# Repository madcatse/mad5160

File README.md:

Добро пожаловать в моqй проект по созданию реплики материнской платы IBM 5160, или как её называют - PC XT. 

**Предыстория**

Как-то вечером, глядя видеоролик Adrain Digital Basement о ремонте оригинальной IBM CGA видеокарты, обратил внимание что в ролике он демонстрировал схему всей видеокарты, которую кто-то выполнил в KiCAD. И упомянул, что схема иначально взята из оригинальной документации самой IBM. У меня сразу возникла мысль - а могу ли я сделать реплику такой видеокарты, раз уже проверенная схема есть в наличии?
Быстрый поиск показал что да, такая схема доступна, а также что кто-то уже сделал реплику CGA видеокарты (проект CGA Redux). Глядя на разведенную карточку, в голову проникла мысль: если есть схема видеокарты от IBM, то наверное есть схема и от материнской платы? И да - IBM 5160 Technical Reference от Апреля 1983 года действительно содержит схему на 11 листах всей материнской платы. Ну а если есть схема - то насколько сложным будет взять её и развести? Сделать реплику. Так появился данный проект.

**Начало работ и поиск подводных камней**

Вооружившись документацией из Technical Reference я принялся за работу. Нашел и скачал всю доступную документацию на 5160, разобрал, и проанализировал. Нашел фотографии материнской платы (спасибо retroweb), с которых бралась визуальная информация по компонентам. 

Потом выписал список всех компонентов на плате, с которыми предстояло работать. В этот список попали:

*центральный процессор и микросхемы, которые составляли его обвязку (чип сет, понимаете?)

*микросхемы памяти, которыми набиралась оперативная память (от 16 килобайт до 256 килобайт)

*микросхемы логики, по большей части представленные 74LS и 74S сериями

*микросхемы ПЗУ, по счастью две обычные 27С256 EPROM

*двойной периферийный драйвер SN75477P

*PAL-чип U44

*мимикрирующие под микросхемы резисторные сборки в DIP-корпусах (RN1-RN5)

*две временные задержки TD1 и TD2

*сравнительно небольшое разнообразие резисторов и конденсаторов, а также кварцевый резонатор

*стандартные 62-пиновые слоты, DIN5-коннектор под клавиатуру и Molex коннектор питания.

**С чем не было проблем**

Меньше всего проблем принес центральный процессор и его обвязка: 
Центральный процессор 8088 (совесткий аналог КР1810ВМ88)
Математический сопроцессор 8087 (чудовищно редкий совесткий аналог КР1810ВМ88)
Программируемый DMA контроллер 8237A (совесткий аналог КР1810ВТ37А)
Программируемый таймер 8253 (совесткий аналог КР580ВИ53Д)
Программируемый интерфейс периферийных устройств 8255A (совесткий аналог КР580ВВ55А)
Программируемый контроллер прерываний 8259A (совесткий аналог КР1810ВН59А)
Генератор частоты 8284A (совесткий аналог КР1810ГФ84А)
Контроллер шины M8288 (совесткий аналог КР1810ВГ88)
Все эти микросхемы сравнительно легкодоступны и их приобретение и проверка не составила никакого труда.

Микросхемы памяти также представляют собой совершенно стандартные 4164/41256 и также не вызывают проблем с их приобретением и проверкой.

То же самое касается и микросхем логики - 74 серия и её советские клоны достаточно распространены, легко приобретаются и проверяются. Неприятность в общем разнообразии микросхем. Для сборки Вам потребуются: 
7407.

74LS00,
74LS04,
74LS04,
74LS10,
74LS20,
74LS27,
74LS32,
74LS138,
74LS158,
74LS175,
74LS243,
74LS244,
74LS245,
74LS322,
74LS373,
74LS670.

74S00,
74S08,
74S74,
74S280.

Часть совершенно свободно находится на aliexpress, часть есть там же, но поддельная, часть найти будет сложно, особенно S-чипы. Но это реализуемо.

Двойной периферийный драйвер _SN75477P_ не относится к 74ой серии, но также легко доступен.

Пассивные компоненты, кварцевый резонатор, подстроеный конденсатор, слоты ISA и коннектор DIN5 для подключения клавиатуры также совершенно стандартные. 

**Проблемы**

Все это касалось комплектующих, с которыми никаких принципиальных проблем не было. К сожалению, это не все компоненты на плате. Есть часть, с которыми проблемы были, и которые пришлось решать.

**PAL 82S129N (U44)**

Злосчастная U44, на месте которой располагается PAL-чип 82S129N, программируемая логическая микросхема декодера памяти. 

Обширный поиск показал отсутствие легкодоступного дампа содержимого данной микросхемы. Однако с давных времен (декабрь 1989 года!) существует мод, 1megXT, который позволяет поставить на старые 5160-материснкие платы до 1 мегабайта памяти, и заключается в замене вышеуказанной 82S129N на GAL16V8 с хорошо задокументированной зашивкой, плюс установке одной дополнительной микросхемы. Установка такого мода мало того что решает проблему с отсутствием зашивки, так ещё и позволяет учетвертить доступный объем оперативной памяти! Хоть я и хотел поиграться с PC с 16кб памяти (минимально возмомжный объем), но как вышло так вышло. 
Для реализации этого мода Вам потребуется одна микросхема GAL16V8 и зашивка для неё. Зашивка с уравнениями присутствует в каталоге firmware\GAL16V8 Там же есть ссылка на оригинальный тред на vcfed. Микросхема GAL16V8 длиннее, чем оригинальная 82S129N, поэтому установить её напрямую не получится. Установите панель на место U44, после чего посадите GAL16V8 так чтобы в панель вошли первый и последний вины, а "хвост" остался висеть в воздухе. Поднимите пины, которые не попали в сокет, и поставьте перемычку между 8 и 10 пинами (это соединит пин земли на GAL16 и пин земли сокета). 

Обратите внимание, что в моем случае я использовал **не свою замену резистороной сборки**, а **оригинальную резисторную сборку**. Так как плата была тестовая, то резисторая сборка ставилась в панель, и она будет мешать моду, не позволяя поставить его по высоте. Надо либо паять плату сборки под основание платы, без панели, либо поднимать микросхему мода несколькими панельками. Если делать без панельки под резисторную сборку, места должно хватить.
После этого мод готов к работе, останется установить джампер на E2 и на блоке SW2 третьим и четвертым переключателем задать необходимый объем оперативной памяти (подробнее см. документацию на мод в файле \firmware\1megXT.txt)

**Резисторные сборки**

IBM установил на плате пять резисторных сборок в DIP-16 корпусах. Это:

RN1, RN5 - 15 резисторов по 4.7 кОм

RN3, RN4 - 8 резисторов по 30 Ом

RN2 - 15 резисторов по 8.2 кОм

Частично такие сборки можно купить, но цены на них очень и очень негуманные. Некоторые (8 по 30) имеют неходовой номинал и представляют собой проблему. Чтобы не заморачиваться с поиском такой экзотики я создал проект "RNDip16", располагающийся в папке \supporting_prj\RNDip16
Проект представляет собой две небольшие платы, по габаритам схожими с футпринтом микросхемы в корпусе DIP-16, на которые можно установить 8 либо 15 SMD-резисторов любого номинала, в корпусе 0805. 

После пайки резисторов следует запаять пины ножек и замена резисторной сборки готова. 

Установка такой замены допускается в сокет, либо напрямую запайкой в плату. Gerber-файлы лежат в папке \supporting_prj\RNDip16\gerbers

**Линии временной задержки TD1 и TD2**

Довольно экзотические компоненты установлены под обозначениями TD1 и TD2. Данные компоненты обеспечивают контролируемую задержку сигнала и являются критичными для корректной работы компьютера. По счастью само IBM в документации от 1986ого года выбросил из схемы TD2, заменив её обычным резистором, убрав резисторы R4 и R5. Но вот TD1 осталась, как и проблемы с ней. Часто на её месте стоят компоненты от BELFUSE 0447-0100-98, либо SPRAGUE 61Z14A100. Это линия задержки на 5 выходов, каждый из которых добавляет 20нс к времени выхода сигнала. На ebay такие компоненты можно купить, однако у нас в настоящий момент это исключено. 

Поиск показал что существуют современные вариации таких задержек - DS1100Z-100 в корпусе NSOIC-8. Я создал проект time_delay, расположенный по пути \supporting_prj\time_delay ,который представляет собой крошечную плату с габаритами исходной временной задержки, на которую необходимо напаять DS1100Z-100 и пины, после чего данный компонент на 100% заменяет исходную временную задержку. 

Gerber-файлы лежат в папке \supporting_prj\time_delay\Gerbers

**Коннектор питания P8/P9**

Старый-добрый AT-коннектор питания (что, получается, неверно, так как у нас XT и этот тип коннектора должен тогда называться XT-коннектор). 

Его можно взять с донорской материнской платы, но я решил поставить современный вариант. Molex 26604060, имеет такие же габариты, но пины квадратной, а не плоской формы. 

Однако типовой AT-блок питания подключается без проблем, и нет нужды искать донора.

**BIOS**

Микросхемы биоса используются совершенно стандартные, 27C256. В одной находится сам биос, в другой - ром с IBM BASIC. Все оригинальные BIOS есть здесь: https://www.minuszerodegrees.net/bios/bios.htm
Также можно использовать различные сторонние BIOS, в частности биос от TurboXT, доступный по пути firmware\turboxt\turboxt.bin

**Ошибки в схеме**

Первая ревизия платы (версия 0.1) содержала в себе ошибку, связанную с опечаткой в оригинальной IBM документации. Для сравнения, фрагмент схемы 1983 года:

Тот же участок в схеме от 1986 года:

Из-за этого линия проверки четности на ISA-слоте была подтянута на +5 постоянно через резистор, и система ВСЕГДА при старте определяла ошибку четности. Это единственный фикс, который потребовалось сделать в схеме после того как был изготовлен, собран и испытан первый образец.

**Печатная плата**

Печатную плату я разводил используя в качестве ориентира скан платы, любезно предоставленный пользователем jafir с форума vcfed, а также остальные референсные фото. Так как оригинальная плата четырехслойная, я не имел на руках оригинальной платы, и тем более не мог сделать послойную декомпозицию платы с целью анализа проводников на внутренних слоях платы, трассировка всех проводников выполнена с нуля. Сигнальные слои - F.Cu и B.Cu. Слой In1.Cu - +5В, слой In2.Cu - земля. Линии +12В, -12В и -5В проведены по сигнальным слоям. Контур платы, координаты посадочных отверстий, некоторые посадочные места компонентов (трехвыводные конденсаторы, пленочный конденсатор, подстроечный конденсатор) взяты из открытого проекта-реплики IBM PC 5150 (PC-Retro, MTM Scientific)

**Изготовление и сборка**

Четырехслойная печатная плата без каких либо особенностей. Изготовление возможно силами китайских производителей. Gerbar-файлы для изготовления находятся по пути \gerbers

**Благодарности**

Выражаю огромное спасибо за идею, помощь в проектировании и отладке:
Adrinan Black с канала Adrian Drigital Basement за идею, а также диагностический ром для памяти, который помог локализовать проблему с Parity

jafir с форума vcfed за качественный скан материнской платы

modem7 с форума vcfed за помощь в локализации проблемы и идеи по исправлению.

**Контакты**

Связаться со мной можно в телеграме, на моем небольшом канале:
https://t.me/madcatse

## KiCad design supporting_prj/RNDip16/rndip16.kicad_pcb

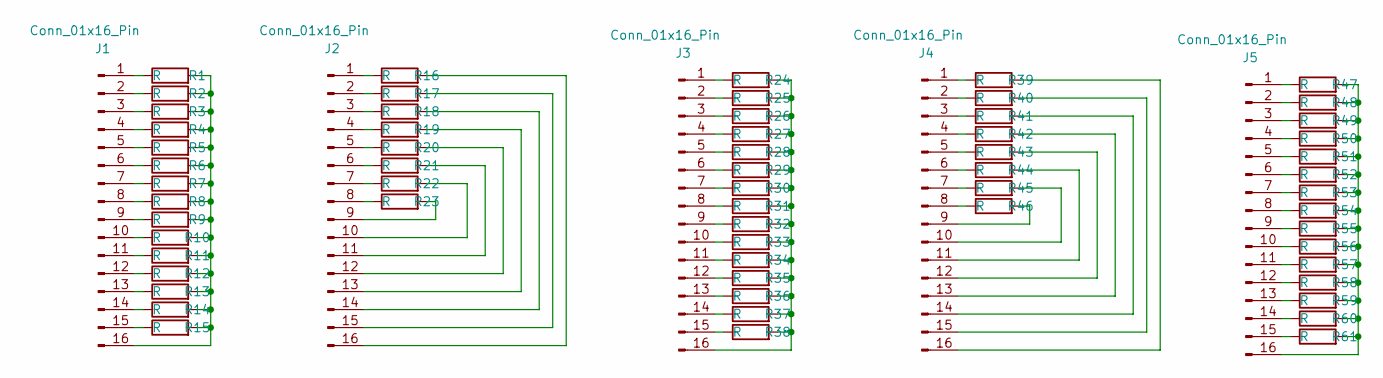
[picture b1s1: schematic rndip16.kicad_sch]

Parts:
J1, J2, J3, J4, J5: Conn_01x16_Pin; Dip16_package
R1, R2, R3, R4, R5, R6, R7, R8, R9, R10, R11, R12, R13, R14, R15, R16, R17, R18, R19, R20, R21, R22, R23, R24, R25, R26, R27, R28, R29, R30, R31, R32, R33, R34, R35, R36, R37, R38, R39, R40, R41, R42, R43, R44, R45, R46, R47, R48, R49, R50, R51, R52, R53, R54, R55, R56, R57, R58, R59, R60, R61: R; R_0805

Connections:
unnamed: J1.1, R1.1
unnamed: J1.2, R2.1
unnamed: J1.3, R3.1
unnamed: J1.4, R4.1
unnamed: J1.5, R5.1
unnamed: J1.6, R6.1
unnamed: J1.7, R7.1
unnamed: J1.8, R8.1
unnamed: J1.9, R9.1
unnamed: J1.10, R10.1
unnamed: J1.11, R11.1
unnamed: J1.12, R12.1
unnamed: J1.13, R13.1
unnamed: J1.14, R14.1
unnamed: J1.15, R15.1
unnamed: J1.16, R1.2, R2.2, R3.2, R4.2, R5.2, R6.2, R7.2, R8.2, R9.2, R10.2, R11.2, R12.2, R13.2, R14.2, R15.2
unnamed: J2.1, R16.1
unnamed: J2.2, R17.1
unnamed: J2.3, R18.1
unnamed: J2.4, R19.1
unnamed: J2.5, R20.1
unnamed: J2.6, R21.1
unnamed: J2.7, R22.1
unnamed: J2.8, R23.1
unnamed: J2.9, R23.2
unnamed: J2.10, R22.2
unnamed: J2.11, R21.2
unnamed: J2.12, R20.2
unnamed: J2.13, R19.2
unnamed: J2.14, R18.2
unnamed: J2.15, R17.2
unnamed: J2.16, R16.2
unnamed: J3.1, R24.1
unnamed: J3.2, R25.1
unnamed: J3.3, R26.1
unnamed: J3.4, R27.1
unnamed: J3.5, R28.1
unnamed: J3.6, R29.1
unnamed: J3.7, R30.1
unnamed: J3.8, R31.1
unnamed: J3.9, R32.1
unnamed: J3.10, R33.1
unnamed: J3.11, R34.1
unnamed: J3.12, R35.1
unnamed: J3.13, R36.1
unnamed: J3.14, R37.1
unnamed: J3.15, R38.1
unnamed: J3.16, R24.2, R25.2, R26.2, R27.2, R28.2, R29.2, R30.2, R31.2, R32.2, R33.2, R34.2, R35.2, R36.2, R37.2, R38.2
unnamed: J4.1, R39.1
unnamed: J4.2, R40.1
unnamed: J4.3, R41.1
unnamed: J4.4, R42.1
unnamed: J4.5, R43.1
unnamed: J4.6, R44.1
unnamed: J4.7, R45.1
unnamed: J4.8, R46.1
unnamed: J4.9, R46.2
unnamed: J4.10, R45.2
unnamed: J4.11, R44.2
unnamed: J4.12, R43.2
unnamed: J4.13, R42.2
unnamed: J4.14, R41.2
unnamed: J4.15, R40.2
unnamed: J4.16, R39.2
unnamed: J5.1, R47.1
unnamed: J5.2, R48.1
unnamed: J5.3, R49.1
unnamed: J5.4, R50.1
unnamed: J5.5, R51.1
unnamed: J5.6, R52.1
unnamed: J5.7, R53.1
unnamed: J5.8, R54.1
unnamed: J5.9, R55.1
unnamed: J5.10, R56.1
unnamed: J5.11, R57.1
unnamed: J5.12, R58.1
unnamed: J5.13, R59.1
unnamed: J5.14, R60.1
unnamed: J5.15, R61.1
unnamed: J5.16, R47.2, R48.2, R49.2, R50.2, R51.2, R52.2, R53.2, R54.2, R55.2, R56.2, R57.2, R58.2, R59.2, R60.2, R61.2

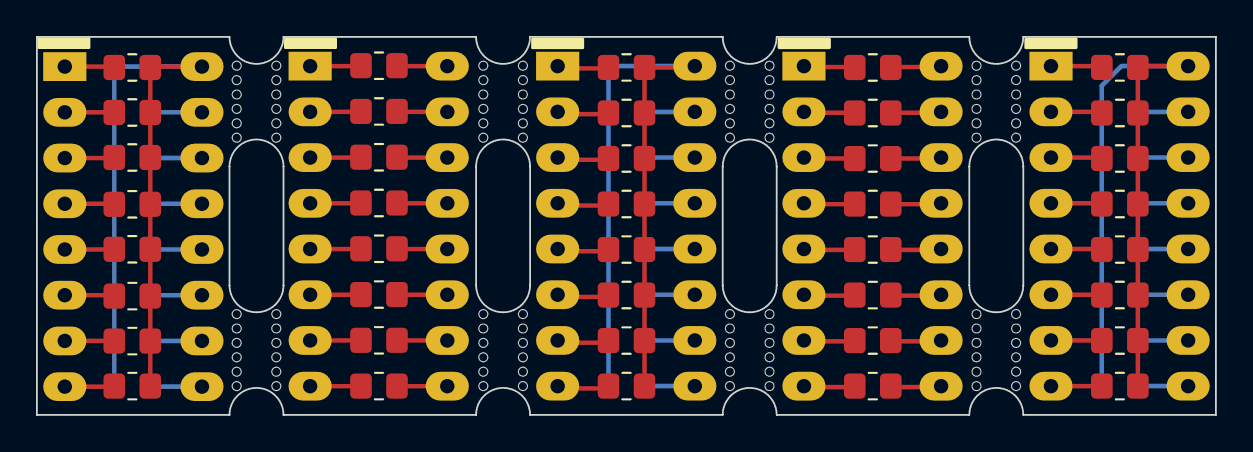
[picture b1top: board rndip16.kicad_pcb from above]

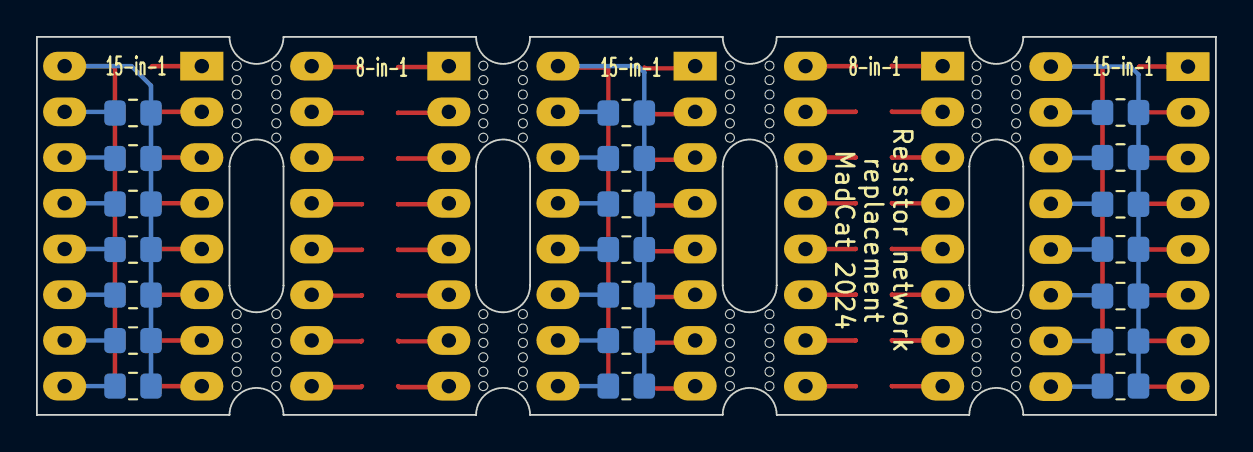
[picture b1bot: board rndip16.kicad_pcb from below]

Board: 2 copper layers, 65.5 x 21.0 mm, 74 parts (21 on the bottom side), 80 nets.

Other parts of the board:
mouse-bite-2.54mm-slot_13, mouse-bite-2.54mm-slot_13#2, mouse-bite-2.54mm-slot_13#3, mouse-bite-2.54mm-slot_13#4, mouse-bite-2.54mm-slot_13#5, mouse-bite-2.54mm-slot_13#6, mouse-bite-2.54mm-slot_13#7, mouse-bite-2.54mm-slot_13#8: VAL**; mouse_bite

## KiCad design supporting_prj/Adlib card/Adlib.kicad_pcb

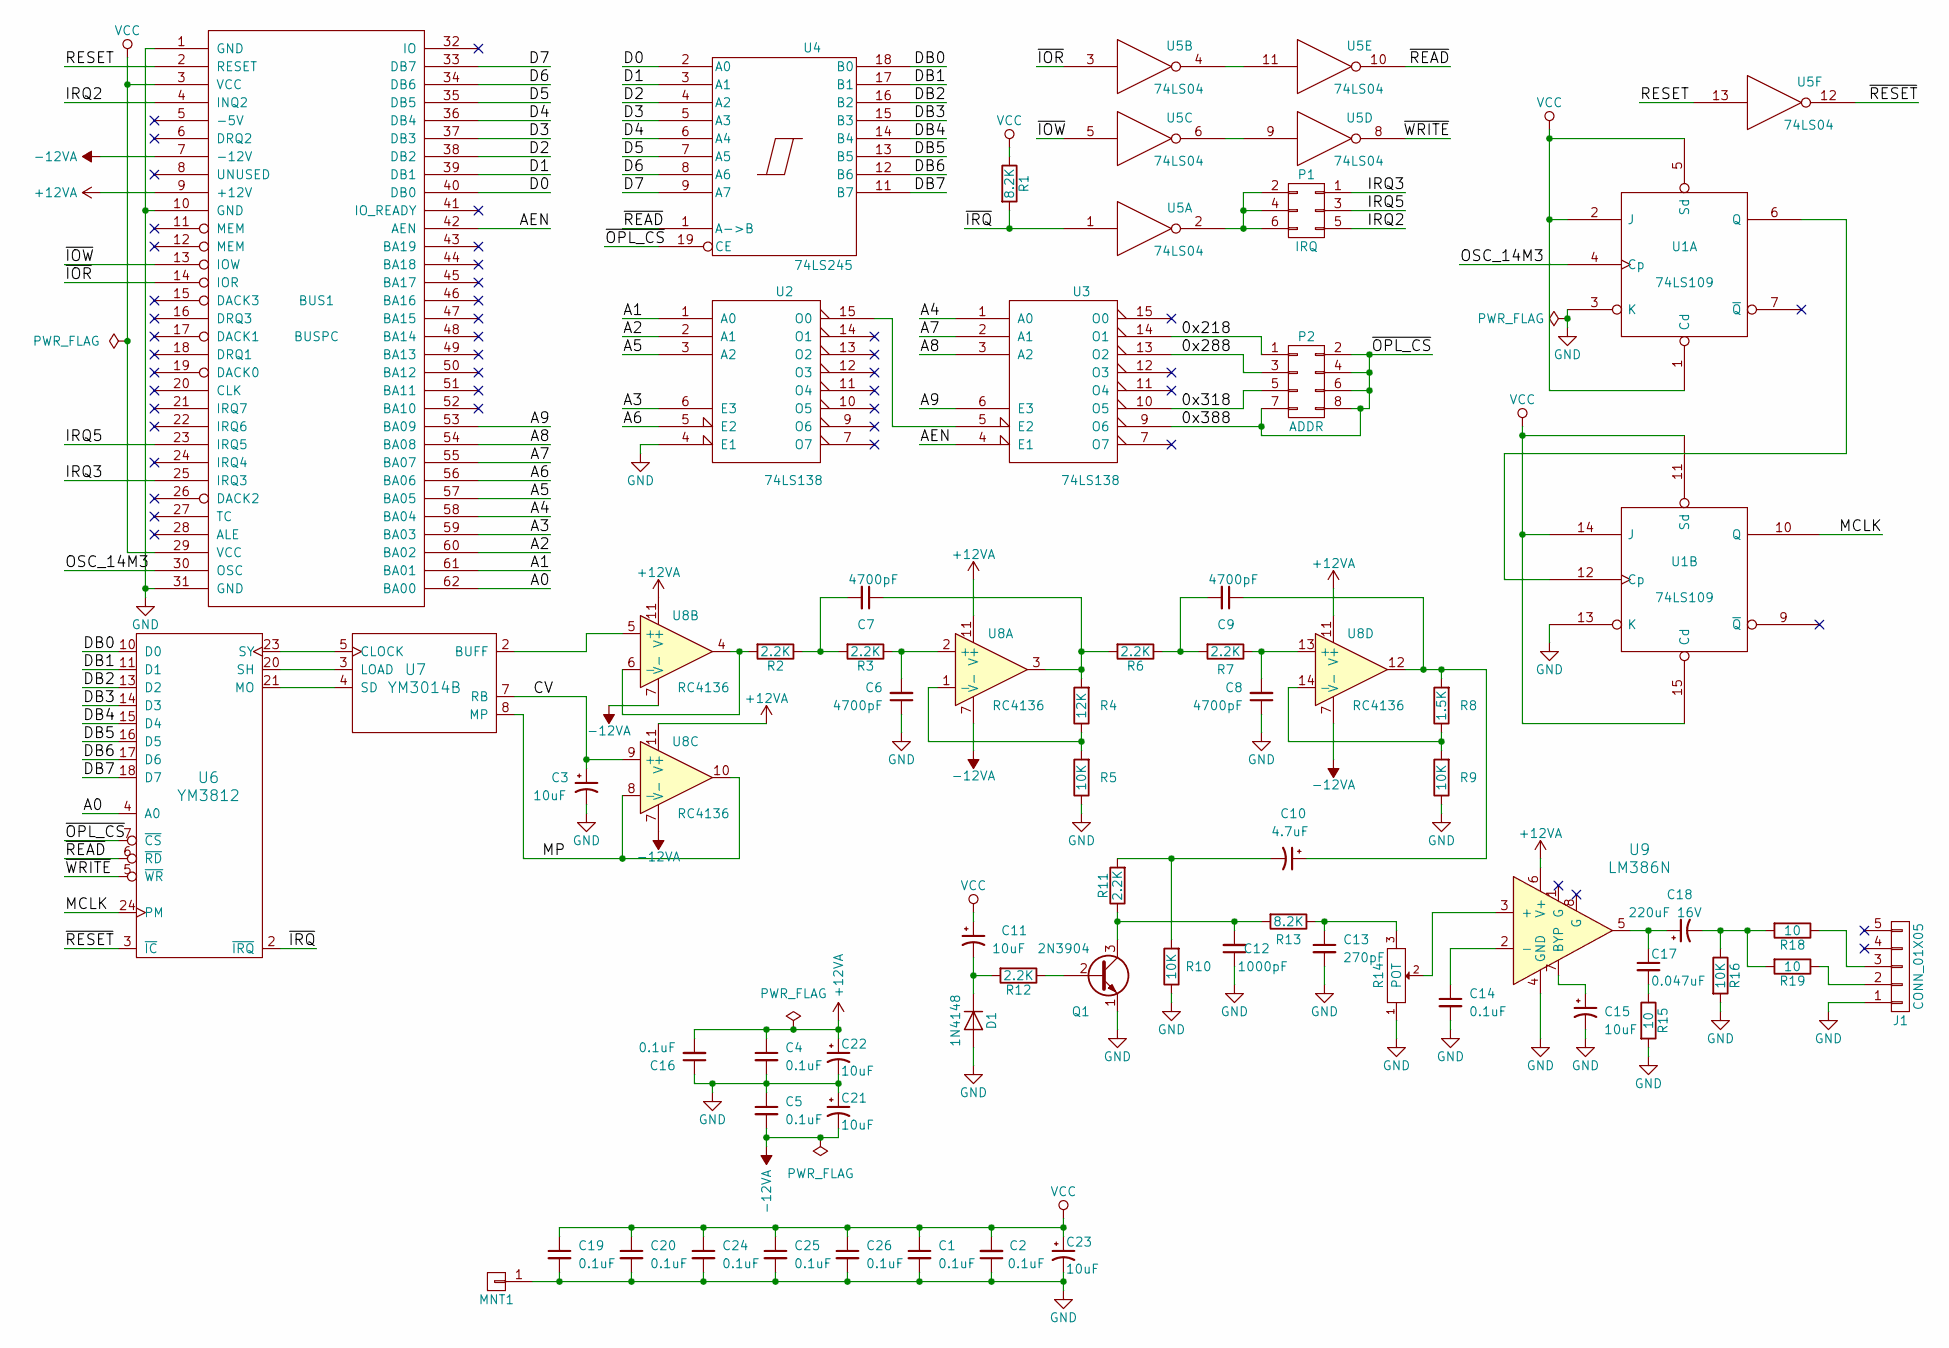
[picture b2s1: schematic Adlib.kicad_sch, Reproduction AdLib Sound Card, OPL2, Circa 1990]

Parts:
BUS1: BUSPC; BUS_PC_ADLIB
C1, C2, C4, C5, C14, C16, C19, C20, C24, C25, C26: 0.1uF; CAP23; Mouser 581-AR215C104K4R
C3, C11, C15, C21, C22, C23: 10uF; CAPAP200; Mouser 581-TAP106M025CRW
C6, C7, C8, C9: 4700pF; CAP23; Mouser 581-AR211C472K4R
C10: 4.7uF; CAPAP200; Mouser 581-TAP475K016SCS
C12: 1000pF; CAP23; Mouser 581-AR211C102K4R
C13: 270pF; CAP23; Mouser 594-S271K43SL0N6TK5R
C17: 0.047uF; CAP23; Mouser 581-AR215C473K4R
C18: 220uF 16V; CAPA1000; Mouser 647-TVX1C221MAD
D1: 1N4148; DIOA500; Mouser 512-1N4148
J1: CONN_01X05; JACK_CUI_SJ1-3553NG; Mouser 490-SJ1-3553NG
MNT1: CONN_01X01; MNT_KEYSTONE_9202; Mouser 534-9202
P1: IRQ; JMP3
P2: ADDR; JMP4
Q1: 2N3904; TO92-IL; Mouser 512-2N3904BU
R1, R13: 8.2K; RESA500; Mouser 291-8.2K-RC
R2, R3, R6, R7, R11, R12: 2.2K; RESA500; Mouser 291-2.2K-RC
R4: 12K; RESA500; Mouser 291-12K-RC
R5, R9, R10, R16: 10K; RESA500; Mouser 291-10K-RC
R8: 1.5K; RESA500; Mouser 291-1.5K-RC
R14: POT; RESV_BOURNS_91A1A; Mouser 652-91A1A-B24-D15L
R15, R18, R19: 10; RESA500; Mouser 291-10-RC
U1: 74LS109; DIP300_16N; Mouser 595-SN74LS109AN
U2, U3: 74LS138; DIP300_16N; Mouser 595-SN74LS138N
U4: 74LS245; DIP300_20N; Mouser 595-SN74LS245N
U5: 74LS04; DIP300_14N; Mouser 595-SN74LS04N
U6: YM3812; DIP600_24N
U7: YM3014B; DIP300_8N
U8: RC4136; DIP300_14N; Mouser 595-RC4136N
U9: LM386N; DIP300_8N; Mouser 926-LM386N-4/NOPB

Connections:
+12VA: BUS1.9 (+12V), C4.1, C16.2, C22.1, U8.11 (V+), U9.6 (V+)
-12VA: BUS1.7 (-12V), C5.2, C21.2, U8.7 (V-)
/0x218: P2.1, U3.14 (O1)
/0x288: P2.3, U3.13 (O2)
/0x318: P2.5, U3.10 (O5)
/0x388: P2.2, P2.4, P2.6, P2.7, P2.8, U3.9 (O6), U4.19 (CE), U6.7 (~CS)
/A0: BUS1.62 (BA00), U6.4 (A0)
/A1: BUS1.61 (BA01), U2.1 (A0)
/A2: BUS1.60 (BA02), U2.2 (A1)
/A3: BUS1.59 (BA03), U2.6 (E3)
/A4: BUS1.58 (BA04), U3.1 (A0)
/A5: BUS1.57 (BA05), U2.3 (A2)
/A6: BUS1.56 (BA06), U2.5 (E2)
/A7: BUS1.55 (BA07), U3.2 (A1)
/A8: BUS1.54 (BA08), U3.3 (A2)
/A9: BUS1.53 (BA09), U3.6 (E3)
/AEN: BUS1.42 (AEN), U3.4 (E1)
/CV: C3.1, U7.7 (RB), U8.9 (+)
/D0: BUS1.40 (DB0), U4.2 (A0)
/D1: BUS1.39 (DB1), U4.3 (A1)
/D2: BUS1.38 (DB2), U4.4 (A2)
/D3: BUS1.37 (DB3), U4.5 (A3)
/D4: BUS1.36 (DB4), U4.6 (A4)
/D5: BUS1.35 (DB5), U4.7 (A5)
/D6: BUS1.34 (DB6), U4.8 (A6)
/D7: BUS1.33 (DB7), U4.9 (A7)
/DB0: U4.18 (B0), U6.10 (D0)
/DB1: U4.17 (B1), U6.11 (D1)
/DB2: U4.16 (B2), U6.13 (D2)
/DB3: U4.15 (B3), U6.14 (D3)
/DB4: U4.14 (B4), U6.15 (D4)
/DB5: U4.13 (B5), U6.16 (D5)
/DB6: U4.12 (B6), U6.17 (D6)
/DB7: U4.11 (B7), U6.18 (D7)
/IRQ2: BUS1.4 (INQ2), P1.5
/IRQ3: BUS1.25 (IRQ3), P1.1
/IRQ5: BUS1.23 (IRQ5), P1.3
/MCLK: U1.10 (Q), U6.24 (PM)
/MP: U7.8 (MP), U8.8 (-), U8.10
/OSC_14M3: BUS1.30 (OSC), U1.4 (Cp)
/RESET: BUS1.2 (RESET), U5.13
/~IOR: BUS1.14 (IOR), U5.3
/~IOW: BUS1.13 (IOW), U5.5
/~IRQ: R1.2, U5.1, U6.2 (~IRQ)
/~READ: U4.1 (A->B), U5.10, U6.6 (~RD)
/~RESET: U5.12, U6.3 (~IC)
/~WRITE: U5.8, U6.5 (~WR)
GND: BUS1.1 (GND), BUS1.10 (GND), BUS1.31 (GND), C1.2, C2.1, C3.2, C4.2, C5.1, C6.1, C8.1, C12.1, C13.2, C14.2, C15.2, C16.1, C19.2, C20.2, C21.1, C22.2, C23.2, C24.2, C25.2, C26.2, D1.2 (A), J1.1, MNT1.1, Q1.1 (E), R5.1, R9.1, R10.1, R14.1, R15.2, R16.2, U1.3 (K), U1.8 (GND), U1.13 (K), U2.4 (E1), U2.8 (GND), U3.8 (GND), U4.10 (GND), U5.7 (GND), U6.12 (GND), U7.6 (GND), U9.4 (GND)
unnamed: C6.2, R3.1, U8.2 (+)
unnamed: C7.1, R4.2, R6.2, U8.3
unnamed: C7.2, R2.1, R3.2
unnamed: C8.2, R7.1, U8.13 (+)
unnamed: C9.2, R6.1, R7.2
unnamed: C9.1, C10.1, R8.2, U8.12
unnamed: C10.2, R10.2, R11.2
unnamed: C11.2, D1.1 (K), R12.2
unnamed: C12.2, Q1.3 (C), R11.1, R13.2
unnamed: C13.1, R13.1, R14.3
unnamed: C14.1, U9.2 (-)
unnamed: C15.1, U9.7 (BYP)
unnamed: C17.1, C18.1, U9.5
unnamed: C17.2, R15.1
unnamed: C18.2, R16.1, R18.2, R19.2
unnamed: J1.2, R19.1
unnamed: J1.3, R18.1
unnamed: P1.2, P1.4, P1.6, U5.2
unnamed: Q1.2 (B), R12.1
unnamed: R2.2, U8.4, U8.6 (-)
unnamed: R4.1, R5.2, U8.1 (-)
unnamed: R8.1, R9.2, U8.14 (-)
unnamed: R14.2, U9.3 (+)
unnamed: U1.6 (Q), U1.12 (Cp)
unnamed: U2.15 (O0), U3.5 (E2)
unnamed: U5.6, U5.9
unnamed: U5.4, U5.11
unnamed: U6.20 (SH), U7.3 (LOAD)
unnamed: U6.21 (MO), U7.4 (SD)
unnamed: U6.23 (SY), U7.5 (CLOCK)
unnamed: U7.2 (BUFF), U8.5 (+)
VCC: BUS1.3 (VCC), BUS1.29 (VCC), C1.1, C2.2, C11.1, C19.1, C20.1, C23.1, C24.1, C25.1, C26.1, R1.1, U1.1 (Cd), U1.2 (J), U1.5 (Sd), U1.11 (Sd), U1.14 (J), U1.15 (Cd), U1.16 (VCC), U2.16 (VCC), U3.16 (VCC), U4.20 (VCC), U5.14 (VCC), U6.1 (VCC), U7.1 (VCC)

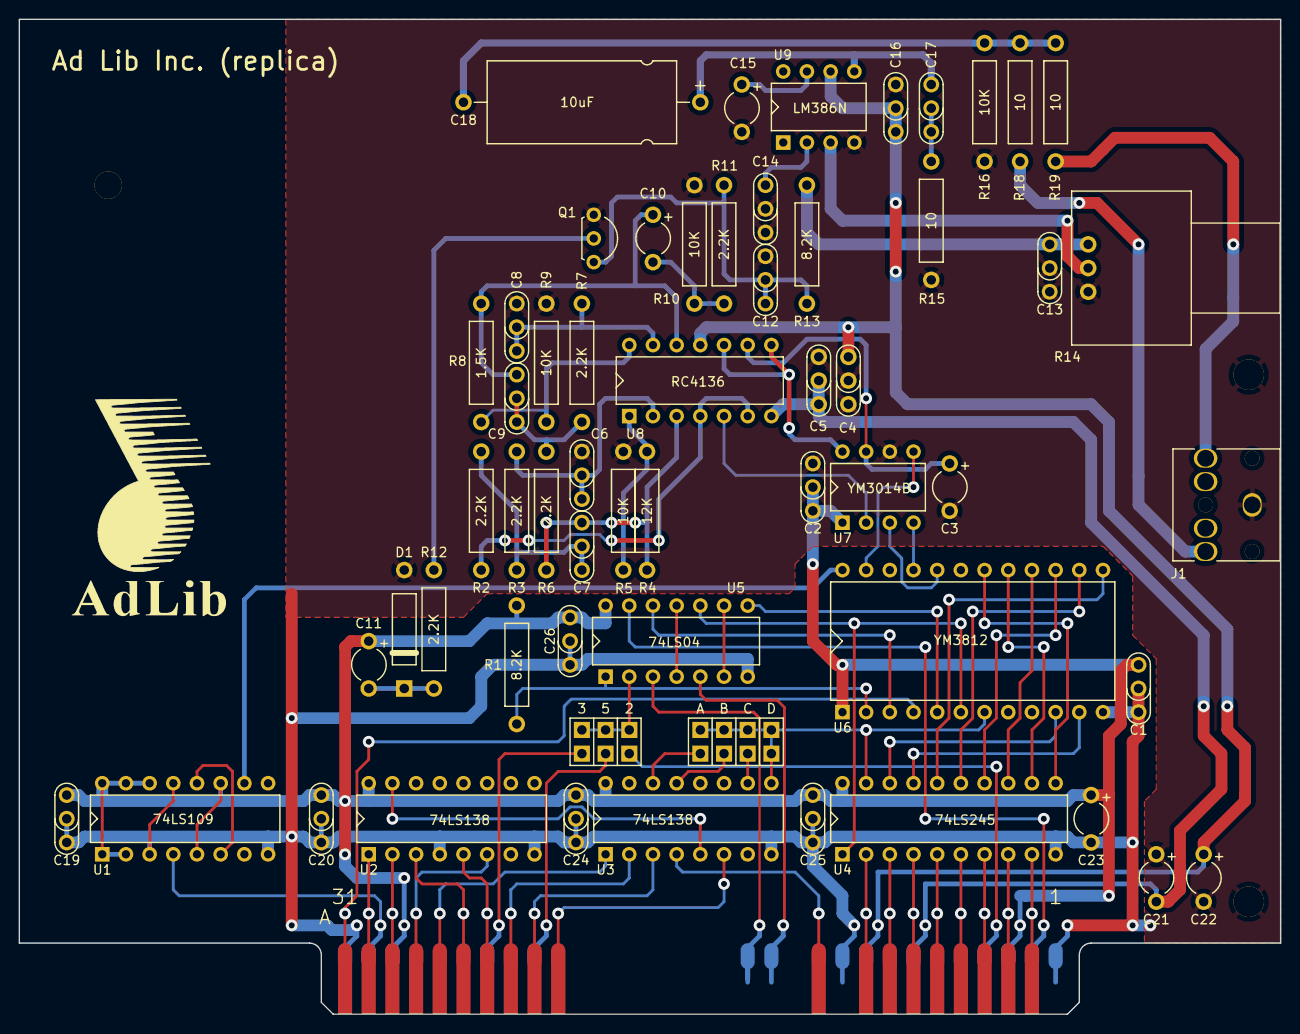
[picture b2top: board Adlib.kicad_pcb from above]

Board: 2 copper layers, 135.3 x 106.7 mm, 60 parts (0 on the bottom side), 80 nets.

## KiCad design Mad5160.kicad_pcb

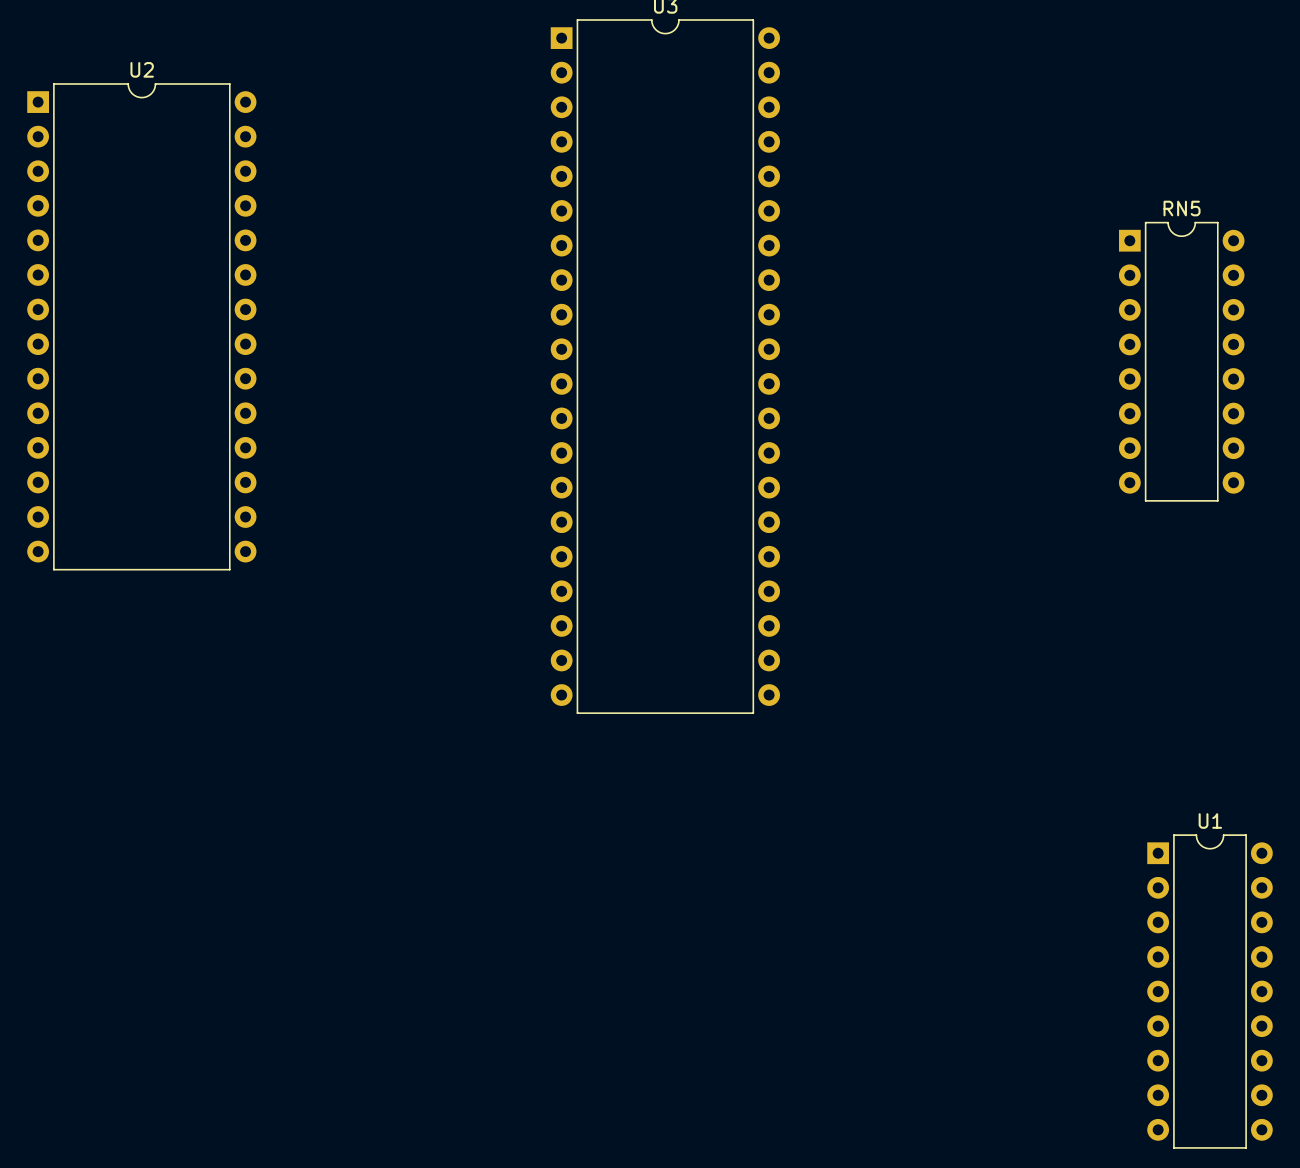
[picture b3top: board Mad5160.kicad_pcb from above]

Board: 2 copper layers, 4 parts (0 on the bottom side), 10 nets, no tracks yet.

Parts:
RN5: 4.7K; DIP-16_W7.62mm
U1: 8284A; DIP-18_W7.62mm
U2: 8259A; DIP-28_W15.24mm
U3: 8088; DIP-40_W15.24mm

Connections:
+5V: RN5.16, U2.28 (Vcc)
unnamed: RN5.7, U2.16 (~SP/~EN)
XD0: U2.11 (D0), U3.19 (CLK)
XD1: U2.10 (D1), U3.21 (RESET)
XD2: U2.9 (D2), U3.17 (NMI)
XD3: U2.8 (D3), U3.16 (AD0)
XD4: U2.7 (D4), U3.15 (AD1)
XD5: U2.6 (D5), U3.14 (AD2)
XD6: U2.5 (D6), U3.13 (AD3)
XD7: U2.4 (D7), U3.12 (AD4)

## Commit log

2024-04-16 Initial upload
2024-04-16 Cleanup
2024-04-16 Update 16.04.2024
    Two datasheets added (8087 and 8288), library updated.
2024-04-18 Firmware for U44 research
2024-04-18 Small update 18.04.2024
2024-04-18 First PCB draw
2024-04-19 Update 19/04
2024-04-19 Adlib project import
2024-04-19 First list finished
2024-04-19 Sheet 2
2024-04-19 Adlib part
2024-04-20 Sheet 2 finished
2024-04-20 3d fixes
2024-04-21 Preparation for Sheet 3
2024-04-22 Working on Sheet3
2024-04-23 Sheet 3 finished
2024-04-23 Sheet 4 preparation
2024-04-23 Sheet 4 finished
2024-04-24 Sheet 5 symbols
2024-04-25 Sheet 5 finished
2024-04-26 Prepare for sheet 6
2024-04-26 Working on sheet 6
2024-04-27 Sheet 7
2024-04-27 Sheet 8 finished
2024-04-27 Prepare for sheet 9
2024-04-28 Sheet 9 finished, almost there
2024-04-29 Sheet 10 done
2024-04-29 At connector
2024-05-01 Update 010502024
2024-05-02 Begin tracing
2024-05-03 Update 03/05/2024
2024-05-09 Tracing for version 1.0 finished
2024-05-12 Tracing finished
2024-05-19 Fixing bugs
2024-05-19 Fixing, fixing...
2024-05-20 Time delay ver1
2024-05-21 Fixing stuff
2024-05-21 Floppy initial upload
2024-05-21 Second tracing added
    Had to retrace the whole board due to lots of changes
2024-05-22 Hyperlynx
2024-05-22 Correction finished
2024-05-26 Gerbers
2024-05-29 Small update
2024-07-29 Schematics
2024-08-07 Version 1.0 fix
2024-08-07 Cleaning projects
2024-08-13 BIOS upload
2024-08-16 firmware
2024-09-22 Cleaning before publishing
    Cleaning before publishing
2024-09-22 Gerbers updated
2024-10-23 RNDip fix
2025-03-20 Smaill updates

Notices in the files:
Adlib card/Adlib.kicad_sch:
Copyright (C) 2017 Eric Schlaepfer
See https://creativecommons.org/licenses/by/4.0
This work is licensed under a Creative Commons Attribution 4.0 International License.
